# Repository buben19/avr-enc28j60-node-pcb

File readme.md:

# IoT node pcb

PCB design for AVR ENC28J60 IoT node board. This repository contains only board
design files, design files for 3D printable case are stored in different repository.

## Features

 - AVR [ATmega328P](http://www.atmel.com/devices/atmega328p.aspx) main microcontroller ([Arduino Pro Mini](https://www.arduino.cc/en/Main/ArduinoBoardProMini)).
 - Ethernet connection with [ENC28J60](http://www.microchip.com/wwwproducts/en/en022889) chip.
 - ENC28J60 powered by mini DC-DC power supply module ([LM2596](http://www.ti.com/lit/ds/symlink/lm2596.pdf) chip).
 - Two RJ-11 connectors for sensors.
 - Powered using  5.5 mm power socket. Central positive,  7-12V.
 - Modular design.
 - Notification LED.
 - Intended  to be manufactured by [dirtypcbs.com](http://dirtypcbs.com/).
 - Optional on board 5V voltage stabilizer. You don't need to rely to voltage stabilizer on Arduino module.

## Images

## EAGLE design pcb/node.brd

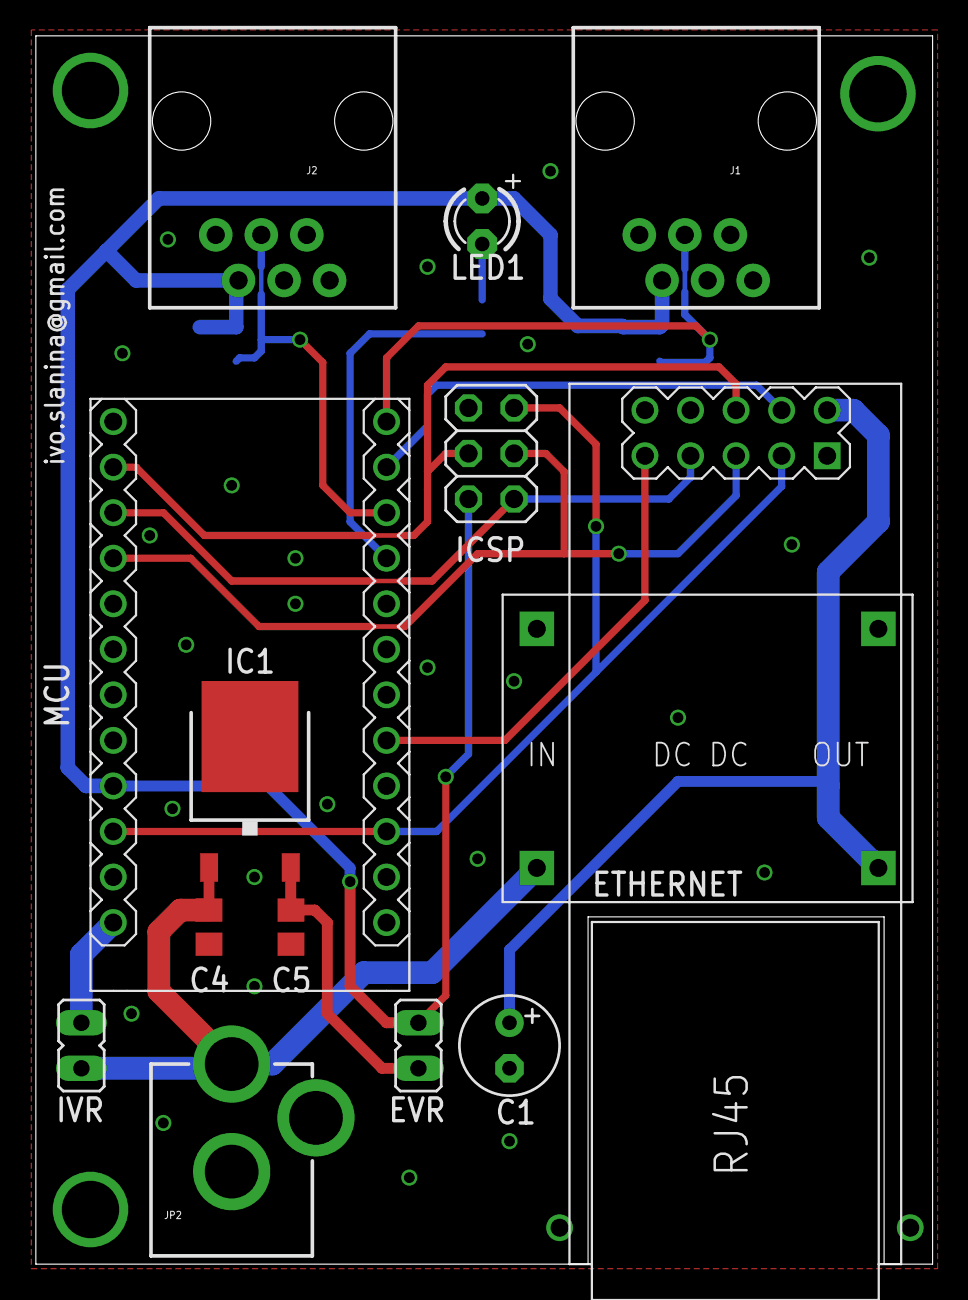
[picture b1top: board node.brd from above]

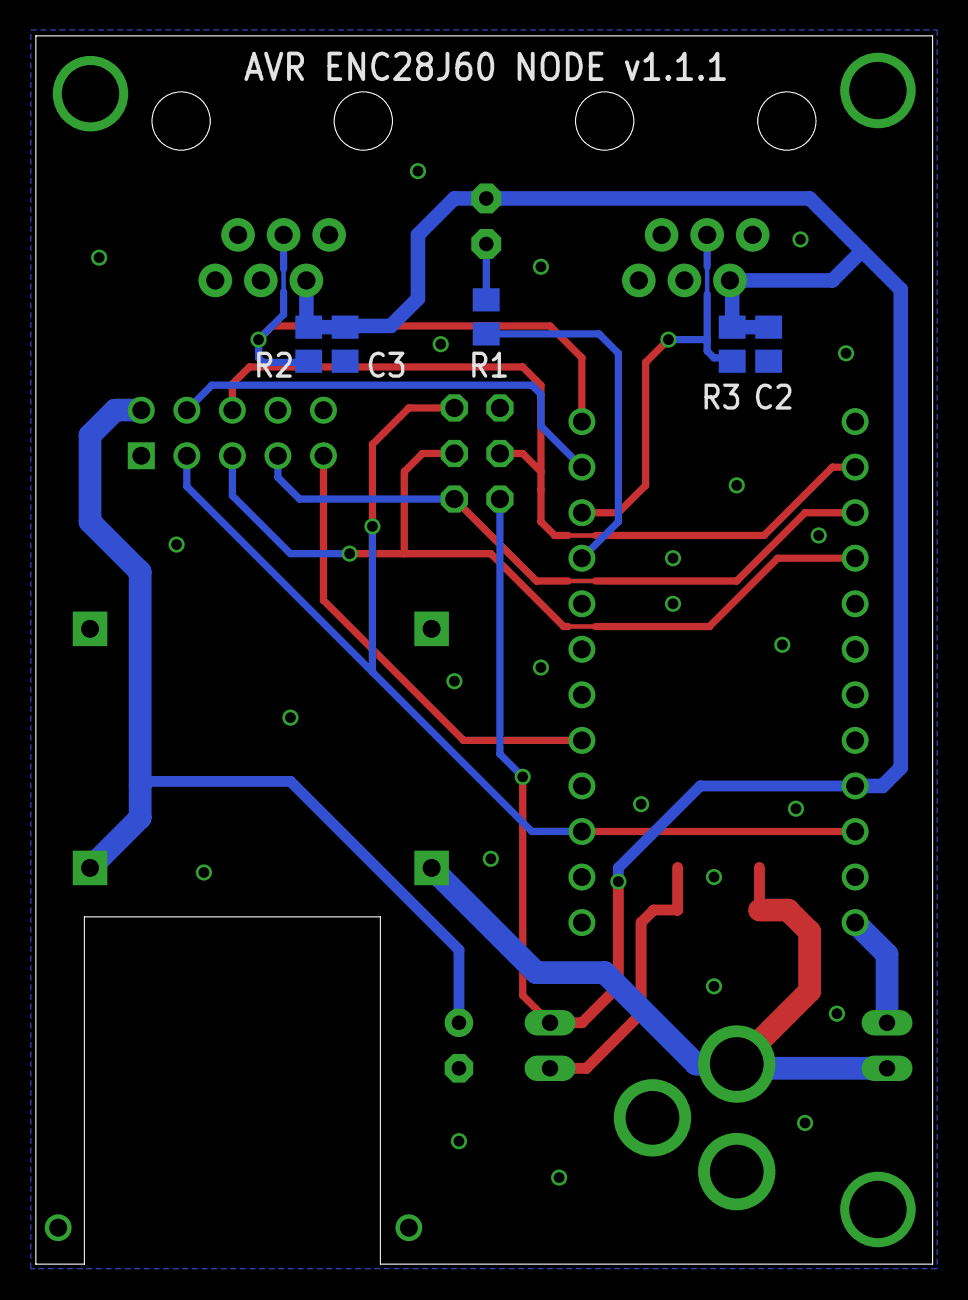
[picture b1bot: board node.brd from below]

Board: 2 copper layers, 50.0 x 68.5 mm, 19 parts (5 on the bottom side), 16 nets.

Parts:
C1: 220uF; E2,5-6
C2, C3, C5: 100nF; C0805
C4: 330nF; C0805
ETHERNET: ETHERNET-ENC28J60-MINI
EVR: JP1
IC1: 7805DT; TO252
ICSP: 2X03
IVR: JP1
J1, J2: RJ11; RJ11-6
JP2: POWER_JACKPTH; POWER_JACK_PTH
LED1: LED3MM
MCU: ARDUINO-PRO-MINI-5.0V#SMP; ARDUINO-PRO-MINI#SMP
R1: 180R; R0805
R2, R3: 10k; R0805
U$2: DC-DC-SMALL; DC-DC

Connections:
+3V3: C1.+, ETHERNET.VCC, U$2.P$2
+5V: C2.1, C3.1, EVR.2, ICSP.2, J1.5, J2.5, LED1.A, MCU.J6.4, R2.2, R3.2
DHT0_SIG: J1.4, MCU.J7.1, R2.1
DHT1_SIG: J2.4, MCU.J7.3, R3.1
ENC28J60_CS: ETHERNET.CS, MCU.J7.2
ENC28J60_DATA_INT: ETHERNET.INT, MCU.J7.8
GND: C1.-, C2.2, C3.2, C4.2, C5.2, ETHERNET.GND, IC1.3, ICSP.6, J1.2, J2.2, JP2.GND, JP2.GNDBREAK, MCU.J6.2, MCU.J7.9, U$2.P$3, U$2.P$4
LED_SINK: MCU.J7.4, R1.2
MISO: ETHERNET.SO, ICSP.1, MCU.J6.10
MOSI: ETHERNET.SI, ICSP.4, MCU.J6.11
unnamed: LED1.K, R1.1
unnamed: IVR.1, MCU.J6.1
unnamed: C5.1, EVR.1, IC1.2
RESET: ETHERNET.RST, ICSP.5, MCU.J6.3, MCU.J7.10
SCK: ETHERNET.SCK, ICSP.3, MCU.J6.9
VIN: C4.1, IC1.1, IVR.2, JP2.PWR, U$2.P$1

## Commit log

2015-11-24 case: first commit
2015-11-24 Fixed case top part.
2016-01-11 New two layer board version (dirtypcbs.com).
2016-01-12 Minor fixes (verion number, signature, added some vias).
2016-01-12 Added gitignore file.
2016-01-12 Changed arduino footprint. Removed drills for unnecessary pins.
2016-01-15 Final release.
2016-02-06 Added STL files.
2016-02-18 Added changelog.
2016-02-18 Removed case.
2016-02-18 Added readme file.
2016-02-22 Some formal changes.
2016-02-22 Changed voltage regulator input capacitor value.
2016-02-22 Changed notification LED current limiting resistor value.
2016-03-23 Added board image and schematic pdf file.
2016-03-23 Added photo of assembled node.
2016-03-23 Updated readme file.
2016-03-23 Updated readme.
2016-03-23 Fixed some part names. Changed board label.
2016-03-23 Updated pdf schematic and board desig image.
2016-03-23 Updated changelog.

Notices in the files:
parts and their libraries:
diy-modules: Released under the Creative Commons Attribution 4.0 International License: http://creativecommons.org/licenses/by/4.0
SparkFun-Connectors: Licensing: Creative Commons ShareAlike 4.0 International - https://creativecommons.org/licenses/by-sa/4.0
